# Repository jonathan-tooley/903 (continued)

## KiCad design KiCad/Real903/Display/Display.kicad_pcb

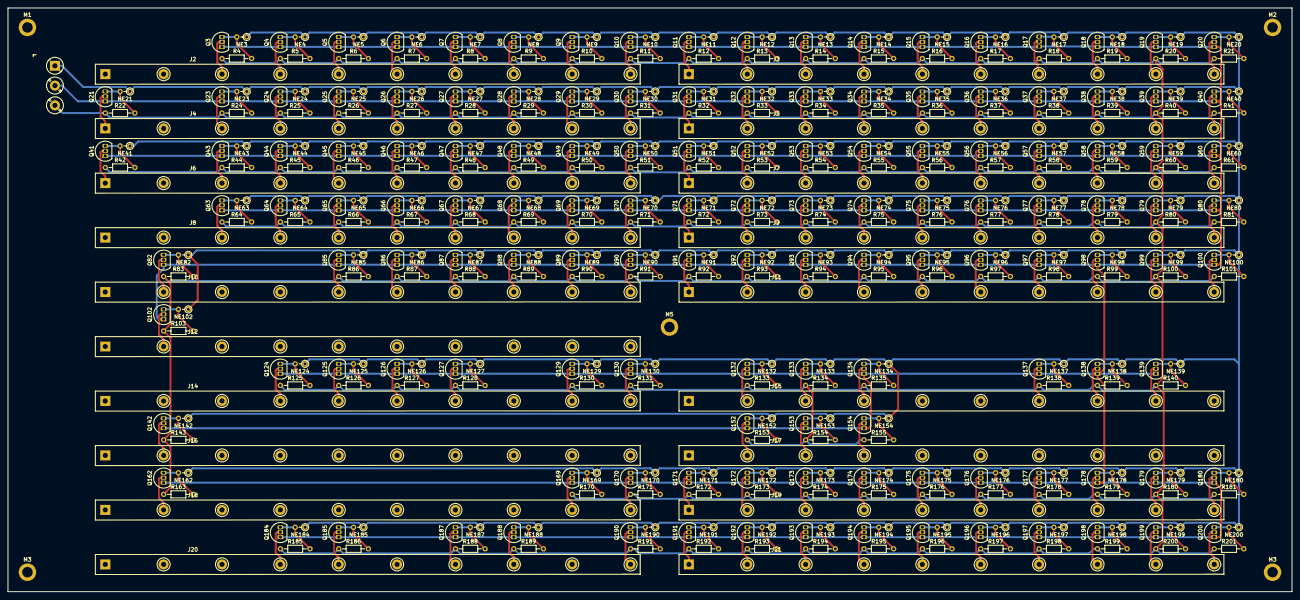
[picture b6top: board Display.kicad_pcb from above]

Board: 2 copper layers, 330.0 x 150.0 mm, 433 parts (0 on the bottom side), 275 nets.

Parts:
J1: TerminalBlock_5.08_1x03
J2, J3, J4, J5, J6, J7, J8, J9, J10, J11, J12, J14, J15, J16, J17, J18, J19, J20, J21: Conn_01x10; DisplayConnector
M1, M2, M3, M3#2, M5: MountingHole_2.7mm_M2.5_ISO14580_Pad
NE3, NE4, NE5, NE6, NE7, NE8, NE9, NE10, NE11, NE12, NE13, NE14, NE15, NE16, NE17, NE18, NE19, NE20, NE21, NE23, NE24, NE25, NE26, NE27, NE28, NE29, NE30, NE31, NE32, NE33, NE34, NE35, NE36, NE37, NE38, NE39, NE40, NE41, NE43, NE44, NE45, NE46, NE47, NE48, NE49, NE50, NE51, NE52, NE53, NE54, NE55, NE56, NE57, NE58, NE59, NE60, NE63, NE64, NE65, NE66, NE67, NE68, NE69, NE70, NE71, NE72, NE73, NE74, NE75, NE76, NE77, NE78, NE79, NE80, NE82, NE85, NE86, NE87, NE88, NE89, NE90, NE91, NE92, NE93, NE94, NE95, NE96, NE97, NE98, NE99, NE100, NE102, NE124, NE125, NE126, NE127, NE129, NE130, NE132, NE133, NE134, NE137, NE138, NE139, NE142, NE152, NE153, NE154, NE162, NE169, NE170, NE171, NE172, NE173, NE174, NE175, NE176, NE177, NE178, NE179, NE180, NE184, NE185, NE187, NE188, NE190, NE191, NE192, NE193, NE194, NE195, NE196, NE197, NE198, NE199, NE200: R_Axial_DIN0204_L3.6mm_D1.6mm_P2.54mm_Vertical
Q3, Q4, Q5, Q6, Q7, Q8, Q9, Q10, Q11, Q12, Q13, Q14, Q15, Q16, Q17, Q18, Q19, Q20, Q21, Q23, Q24, Q25, Q26, Q27, Q28, Q29, Q30, Q31, Q32, Q33, Q34, Q35, Q36, Q37, Q38, Q39, Q40, Q41, Q43, Q44, Q45, Q46, Q47, Q48, Q49, Q50, Q51, Q52, Q53, Q54, Q55, Q56, Q57, Q58, Q59, Q60, Q63, Q64, Q65, Q66, Q67, Q68, Q69, Q70, Q71, Q72, Q73, Q74, Q75, Q76, Q77, Q78, Q79, Q80, Q82, Q85, Q86, Q87, Q88, Q89, Q90, Q91, Q92, Q93, Q94, Q95, Q96, Q97, Q98, Q99, Q100, Q102, Q124, Q125, Q126, Q127, Q129, Q130, Q132, Q133, Q134, Q137, Q138, Q139, Q142, Q152, Q153, Q154, Q162, Q169, Q170, Q171, Q172, Q173, Q174, Q175, Q176, Q177, Q178, Q179, Q180, Q184, Q185, Q187, Q188, Q190, Q191, Q192, Q193, Q194, Q195, Q196, Q197, Q198, Q199, Q200: TO-92L_Inline
R4, R5, R6, R7, R8, R9, R10, R11, R12, R13, R14, R15, R16, R17, R18, R19, R20, R21, R22, R24, R25, R26, R27, R28, R29, R30, R31, R32, R33, R34, R35, R36, R37, R38, R39, R40, R41, R42, R44, R45, R46, R47, R48, R49, R50, R51, R52, R53, R54, R55, R56, R57, R58, R59, R60, R61, R64, R65, R66, R67, R68, R69, R70, R71, R72, R73, R74, R75, R76, R77, R78, R79, R80, R81, R83, R86, R87, R88, R89, R90, R91, R92, R93, R94, R95, R96, R97, R98, R99, R100, R101, R103, R125, R126, R127, R128, R130, R131, R133, R134, R135, R138, R139, R140, R143, R153, R154, R155, R163, R170, R171, R172, R173, R174, R175, R176, R177, R178, R179, R180, R181, R185, R186, R188, R189, R191, R192, R193, R194, R195, R196, R197, R198, R199, R200, R201: 82k; R_Axial_DIN0204_L3.6mm_D1.6mm_P7.62mm_Horizontal

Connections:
0v: J1.2, Q3.1, Q4.1, Q5.1, Q6.1, Q7.1, Q8.1, Q9.1, Q10.1, Q11.1, Q12.1, Q13.1, Q14.1, Q15.1, Q16.1, Q17.1, Q18.1, Q19.1, Q20.1, Q21.1, Q23.1, Q24.1, Q25.1, Q26.1, Q27.1, Q28.1, Q29.1, Q30.1, Q31.1, Q32.1, Q33.1, Q34.1, Q35.1, Q36.1, Q37.1, Q38.1, Q39.1, Q40.1, Q41.1, Q43.1, Q44.1, Q45.1, Q46.1, Q47.1, Q48.1, Q49.1, Q50.1, Q51.1, Q52.1, Q53.1, Q54.1, Q55.1, Q56.1, Q57.1, Q58.1, Q59.1, Q60.1, Q63.1, Q64.1, Q65.1, Q66.1, Q67.1, Q68.1, Q69.1, Q70.1, Q71.1, Q72.1, Q73.1, Q74.1, Q75.1, Q76.1, Q77.1, Q78.1, Q79.1, Q80.1, Q82.1, Q85.1, Q86.1, Q87.1, Q88.1, Q89.1, Q90.1, Q91.1, Q92.1, Q93.1, Q94.1, Q95.1, Q96.1, Q97.1, Q98.1, Q99.1, Q100.1, Q102.1, Q124.1, Q125.1, Q126.1, Q127.1, Q129.1, Q130.1, Q132.1, Q133.1, Q134.1, Q137.1, Q138.1, Q139.1, Q142.1, Q152.1, Q153.1, Q154.1, Q162.1, Q169.1, Q170.1, Q171.1, Q172.1, Q173.1, Q174.1, Q175.1, Q176.1, Q177.1, Q178.1, Q179.1, Q180.1, Q184.1, Q185.1, Q187.1, Q188.1, Q190.1, Q191.1, Q192.1, Q193.1, Q194.1, Q195.1, Q196.1, Q197.1, Q198.1, Q199.1, Q200.1
+70v: J1.3, R4.1, R5.1, R6.1, R7.1, R8.1, R9.1, R10.1, R11.1, R12.1, R13.1, R14.1, R15.1, R16.1, R17.1, R18.1, R19.1, R20.1, R21.1, R22.1, R24.1, R25.1, R26.1, R27.1, R28.1, R29.1, R30.1, R31.1, R32.1, R33.1, R34.1, R35.1, R36.1, R37.1, R38.1, R39.1, R40.1, R41.1, R42.1, R44.1, R45.1, R46.1, R47.1, R48.1, R49.1, R50.1, R51.1, R52.1, R53.1, R54.1, R55.1, R56.1, R57.1, R58.1, R59.1, R60.1, R61.1, R64.1, R65.1, R66.1, R67.1, R68.1, R69.1, R70.1, R71.1, R72.1, R73.1, R74.1, R75.1, R76.1, R77.1, R78.1, R79.1, R80.1, R81.1, R83.1, R86.1, R87.1, R88.1, R89.1, R90.1, R91.1, R92.1, R93.1, R94.1, R95.1, R96.1, R97.1, R98.1, R99.1, R100.1, R101.1, R103.1, R125.1, R126.1, R127.1, R128.1, R130.1, R131.1, R133.1, R134.1, R135.1, R138.1, R139.1, R140.1, R143.1, R153.1, R154.1, R155.1, R163.1, R170.1, R171.1, R172.1, R173.1, R174.1, R175.1, R176.1, R177.1, R178.1, R179.1, R180.1, R181.1, R185.1, R186.1, R188.1, R189.1, R191.1, R192.1, R193.1, R194.1, R195.1, R196.1, R197.1, R198.1, R199.1, R200.1, R201.1
-40v: J1.1, NE3.1, NE4.1, NE5.1, NE6.1, NE7.1, NE8.1, NE9.1, NE10.1, NE11.1, NE12.1, NE13.1, NE14.1, NE15.1, NE16.1, NE17.1, NE18.1, NE19.1, NE20.1, NE21.1, NE23.1, NE24.1, NE25.1, NE26.1, NE27.1, NE28.1, NE29.1, NE30.1, NE31.1, NE32.1, NE33.1, NE34.1, NE35.1, NE36.1, NE37.1, NE38.1, NE39.1, NE40.1, NE41.1, NE43.1, NE44.1, NE45.1, NE46.1, NE47.1, NE48.1, NE49.1, NE50.1, NE51.1, NE52.1, NE53.1, NE54.1, NE55.1, NE56.1, NE57.1, NE58.1, NE59.1, NE60.1, NE63.1, NE64.1, NE65.1, NE66.1, NE67.1, NE68.1, NE69.1, NE70.1, NE71.1, NE72.1, NE73.1, NE74.1, NE75.1, NE76.1, NE77.1, NE78.1, NE79.1, NE80.1, NE82.1, NE85.1, NE86.1, NE87.1, NE88.1, NE89.1, NE90.1, NE91.1, NE92.1, NE93.1, NE94.1, NE95.1, NE96.1, NE97.1, NE98.1, NE99.1, NE100.1, NE102.1, NE124.1, NE125.1, NE126.1, NE127.1, NE129.1, NE130.1, NE132.1, NE133.1, NE134.1, NE137.1, NE138.1, NE139.1, NE142.1, NE152.1, NE153.1, NE154.1, NE162.1, NE169.1, NE170.1, NE171.1, NE172.1, NE173.1, NE174.1, NE175.1, NE176.1, NE177.1, NE178.1, NE179.1, NE180.1, NE184.1, NE185.1, NE187.1, NE188.1, NE190.1, NE191.1, NE192.1, NE193.1, NE194.1, NE195.1, NE196.1, NE197.1, NE198.1, NE199.1, NE200.1
unnamed: J2.3, Q3.2
unnamed: J2.4, Q4.2
unnamed: J2.5, Q5.2
unnamed: J2.6, Q6.2
unnamed: J2.7, Q7.2
unnamed: J2.8, Q8.2
unnamed: J2.9, Q9.2
unnamed: J2.10, Q10.2
unnamed: J3.1, Q11.2
unnamed: J3.2, Q12.2
unnamed: J3.3, Q13.2
unnamed: J3.4, Q14.2
unnamed: J3.5, Q15.2
unnamed: J3.6, Q16.2
unnamed: J3.7, Q17.2
unnamed: J3.8, Q18.2
unnamed: J3.9, Q19.2
unnamed: J3.10, Q20.2
unnamed: J4.1, Q21.2
unnamed: J4.3, Q23.2
unnamed: J4.4, Q24.2
unnamed: J4.5, Q25.2
unnamed: J4.6, Q26.2
unnamed: J4.7, Q27.2
unnamed: J4.8, Q28.2
unnamed: J4.9, Q29.2
unnamed: J4.10, Q30.2
unnamed: J5.1, Q31.2
unnamed: J5.2, Q32.2
unnamed: J5.3, Q33.2
unnamed: J5.4, Q34.2
unnamed: J5.5, Q35.2
unnamed: J5.6, Q36.2
unnamed: J5.7, Q37.2
unnamed: J5.8, Q38.2
unnamed: J5.9, Q39.2
unnamed: J5.10, Q40.2
unnamed: J6.1, Q41.2
unnamed: J6.3, Q43.2
unnamed: J6.4, Q44.2
unnamed: J6.5, Q45.2
unnamed: J6.6, Q46.2
unnamed: J6.7, Q47.2
unnamed: J6.8, Q48.2
unnamed: J6.9, Q49.2
unnamed: J6.10, Q50.2
unnamed: J7.1, Q51.2
unnamed: J7.2, Q52.2
unnamed: J7.3, Q53.2
unnamed: J7.4, Q54.2
unnamed: J7.5, Q55.2
unnamed: J7.6, Q56.2
unnamed: J7.7, Q57.2
unnamed: J7.8, Q58.2
unnamed: J7.9, Q59.2
unnamed: J7.10, Q60.2
unnamed: J8.3, Q63.2
unnamed: J8.4, Q64.2
unnamed: J8.5, Q65.2
unnamed: J8.6, Q66.2
unnamed: J8.7, Q67.2
unnamed: J8.8, Q68.2
unnamed: J8.9, Q69.2
unnamed: J8.10, Q70.2
unnamed: J9.1, Q71.2
unnamed: J9.2, Q72.2
unnamed: J9.3, Q73.2
unnamed: J9.4, Q74.2
unnamed: J9.5, Q75.2
unnamed: J9.6, Q76.2
unnamed: J9.7, Q77.2
unnamed: J9.8, Q78.2
unnamed: J9.9, Q79.2
unnamed: J9.10, Q80.2
unnamed: J10.2, Q82.2
unnamed: J10.5, Q85.2
unnamed: J10.6, Q86.2
unnamed: J10.7, Q87.2
unnamed: J10.8, Q88.2
unnamed: J10.9, Q89.2
unnamed: J10.10, Q90.2
unnamed: J11.1, Q91.2
unnamed: J11.2, Q92.2
unnamed: J11.3, Q93.2
unnamed: J11.4, Q94.2
unnamed: J11.5, Q95.2
unnamed: J11.6, Q96.2
unnamed: J11.7, Q97.2
unnamed: J11.8, Q98.2
unnamed: J11.9, Q99.2
unnamed: J11.10, Q100.2
unnamed: J12.2, Q102.2
unnamed: J14.4, Q124.2
unnamed: J14.5, Q125.2
unnamed: J14.6, Q126.2
unnamed: J14.7, Q127.2
unnamed: J14.9, Q129.2
unnamed: J14.10, Q130.2
unnamed: J15.2, Q132.2
unnamed: J15.3, Q133.2
unnamed: J15.4, Q134.2
unnamed: J15.7, Q137.2
unnamed: J15.8, Q138.2
unnamed: J15.9, Q139.2
unnamed: J16.2, Q142.2
unnamed: J17.2, Q152.2
unnamed: J17.3, Q153.2
unnamed: J17.4, Q154.2
unnamed: J18.2, Q162.2
unnamed: J18.9, Q169.2
unnamed: J18.10, Q170.2
unnamed: J19.1, Q171.2
unnamed: J19.2, Q172.2
unnamed: J19.3, Q173.2
unnamed: J19.4, Q174.2
unnamed: J19.5, Q175.2
unnamed: J19.6, Q176.2
unnamed: J19.7, Q177.2
unnamed: J19.8, Q178.2
unnamed: J19.9, Q179.2
unnamed: J19.10, Q180.2
unnamed: J20.4, Q184.2
unnamed: J20.5, Q185.2
unnamed: J20.7, Q187.2
unnamed: J20.8, Q188.2
unnamed: J20.10, Q190.2
unnamed: J21.1, Q191.2
unnamed: J21.2, Q192.2
unnamed: J21.3, Q193.2
unnamed: J21.4, Q194.2
unnamed: J21.5, Q195.2
unnamed: J21.6, Q196.2
unnamed: J21.7, Q197.2
unnamed: J21.8, Q198.2
unnamed: J21.9, Q199.2
unnamed: J21.10, Q200.2
unnamed: NE3.2, Q3.3, R4.2
unnamed: NE4.2, Q4.3, R5.2
unnamed: NE5.2, Q5.3, R6.2
unnamed: NE6.2, Q6.3, R7.2
unnamed: NE7.2, Q7.3, R8.2
unnamed: NE8.2, Q8.3, R9.2
unnamed: NE9.2, Q9.3, R10.2
unnamed: NE10.2, Q10.3, R11.2
unnamed: NE11.2, Q11.3, R12.2
unnamed: NE12.2, Q12.3, R13.2
unnamed: NE13.2, Q13.3, R14.2
unnamed: NE14.2, Q14.3, R15.2
unnamed: NE15.2, Q15.3, R16.2
unnamed: NE16.2, Q16.3, R17.2
unnamed: NE17.2, Q17.3, R18.2
unnamed: NE18.2, Q18.3, R19.2
unnamed: NE19.2, Q19.3, R20.2
unnamed: NE20.2, Q20.3, R21.2
unnamed: NE21.2, Q21.3, R22.2
unnamed: NE23.2, Q23.3, R24.2
unnamed: NE24.2, Q24.3, R25.2
unnamed: NE25.2, Q25.3, R26.2
unnamed: NE26.2, Q26.3, R27.2
unnamed: NE27.2, Q27.3, R28.2
unnamed: NE28.2, Q28.3, R29.2
unnamed: NE29.2, Q29.3, R30.2
unnamed: NE30.2, Q30.3, R31.2
unnamed: NE31.2, Q31.3, R32.2
unnamed: NE32.2, Q32.3, R33.2
unnamed: NE33.2, Q33.3, R34.2
unnamed: NE34.2, Q34.3, R35.2
unnamed: NE35.2, Q35.3, R36.2
unnamed: NE36.2, Q36.3, R37.2
unnamed: NE37.2, Q37.3, R38.2
unnamed: NE38.2, Q38.3, R39.2
unnamed: NE39.2, Q39.3, R40.2
unnamed: NE40.2, Q40.3, R41.2
unnamed: NE41.2, Q41.3, R42.2
unnamed: NE43.2, Q43.3, R44.2
unnamed: NE44.2, Q44.3, R45.2
unnamed: NE45.2, Q45.3, R46.2
unnamed: NE46.2, Q46.3, R47.2
unnamed: NE47.2, Q47.3, R48.2
unnamed: NE48.2, Q48.3, R49.2
unnamed: NE49.2, Q49.3, R50.2
unnamed: NE50.2, Q50.3, R51.2
unnamed: NE51.2, Q51.3, R52.2
unnamed: NE52.2, Q52.3, R53.2
unnamed: NE53.2, Q53.3, R54.2
unnamed: NE54.2, Q54.3, R55.2
unnamed: NE55.2, Q55.3, R56.2
unnamed: NE56.2, Q56.3, R57.2
unnamed: NE57.2, Q57.3, R58.2
unnamed: NE58.2, Q58.3, R59.2
unnamed: NE59.2, Q59.3, R60.2
unnamed: NE60.2, Q60.3, R61.2
unnamed: NE63.2, Q63.3, R64.2
unnamed: NE64.2, Q64.3, R65.2
unnamed: NE65.2, Q65.3, R66.2
unnamed: NE66.2, Q66.3, R67.2
unnamed: NE67.2, Q67.3, R68.2
unnamed: NE68.2, Q68.3, R69.2
unnamed: NE69.2, Q69.3, R70.2
unnamed: NE70.2, Q70.3, R71.2
unnamed: NE71.2, Q71.3, R72.2
unnamed: NE72.2, Q72.3, R73.2
unnamed: NE73.2, Q73.3, R74.2
unnamed: NE74.2, Q74.3, R75.2
unnamed: NE75.2, Q75.3, R76.2
unnamed: NE76.2, Q76.3, R77.2
unnamed: NE77.2, Q77.3, R78.2
unnamed: NE78.2, Q78.3, R79.2
unnamed: NE79.2, Q79.3, R80.2
unnamed: NE80.2, Q80.3, R81.2
unnamed: NE82.2, Q82.3, R83.2
unnamed: NE85.2, Q85.3, R86.2
unnamed: NE86.2, Q86.3, R87.2
unnamed: NE87.2, Q87.3, R88.2
unnamed: NE88.2, Q88.3, R89.2
unnamed: NE89.2, Q89.3, R90.2
unnamed: NE90.2, Q90.3, R91.2
unnamed: NE91.2, Q91.3, R92.2
unnamed: NE92.2, Q92.3, R93.2
unnamed: NE93.2, Q93.3, R94.2
unnamed: NE94.2, Q94.3, R95.2
unnamed: NE95.2, Q95.3, R96.2
unnamed: NE96.2, Q96.3, R97.2
unnamed: NE97.2, Q97.3, R98.2
unnamed: NE98.2, Q98.3, R99.2
unnamed: NE99.2, Q99.3, R100.2
unnamed: NE100.2, Q100.3, R101.2
unnamed: NE102.2, Q102.3, R103.2
unnamed: NE124.2, Q124.3, R125.2
unnamed: NE125.2, Q125.3, R126.2
unnamed: NE126.2, Q126.3, R127.2
unnamed: NE127.2, Q127.3, R128.2
unnamed: NE129.2, Q129.3, R130.2
unnamed: NE130.2, Q130.3, R131.2
unnamed: NE132.2, Q132.3, R133.2
unnamed: NE133.2, Q133.3, R134.2
unnamed: NE134.2, Q134.3, R135.2
unnamed: NE137.2, Q137.3, R138.2
unnamed: NE138.2, Q138.3, R139.2
unnamed: NE139.2, Q139.3, R140.2
unnamed: NE142.2, Q142.3, R143.2
unnamed: NE152.2, Q152.3, R153.2
unnamed: NE153.2, Q153.3, R154.2
unnamed: NE154.2, Q154.3, R155.2
unnamed: NE162.2, Q162.3, R163.2
unnamed: NE169.2, Q169.3, R170.2
unnamed: NE170.2, Q170.3, R171.2
unnamed: NE171.2, Q171.3, R172.2
unnamed: NE172.2, Q172.3, R173.2
unnamed: NE173.2, Q173.3, R174.2
unnamed: NE174.2, Q174.3, R175.2
unnamed: NE175.2, Q175.3, R176.2
unnamed: NE176.2, Q176.3, R177.2
unnamed: NE177.2, Q177.3, R178.2
unnamed: NE178.2, Q178.3, R179.2
unnamed: NE179.2, Q179.3, R180.2
unnamed: NE180.2, Q180.3, R181.2
unnamed: NE184.2, Q184.3, R185.2
unnamed: NE185.2, Q185.3, R186.2
unnamed: NE187.2, Q187.3, R188.2
unnamed: NE188.2, Q188.3, R189.2
unnamed: NE190.2, Q190.3, R191.2
unnamed: NE191.2, Q191.3, R192.2
unnamed: NE192.2, Q192.3, R193.2
unnamed: NE193.2, Q193.3, R194.2
unnamed: NE194.2, Q194.3, R195.2
unnamed: NE195.2, Q195.3, R196.2
unnamed: NE196.2, Q196.3, R197.2
unnamed: NE197.2, Q197.3, R198.2
unnamed: NE198.2, Q198.3, R199.2
unnamed: NE199.2, Q199.3, R200.2
unnamed: NE200.2, Q200.3, R201.2
